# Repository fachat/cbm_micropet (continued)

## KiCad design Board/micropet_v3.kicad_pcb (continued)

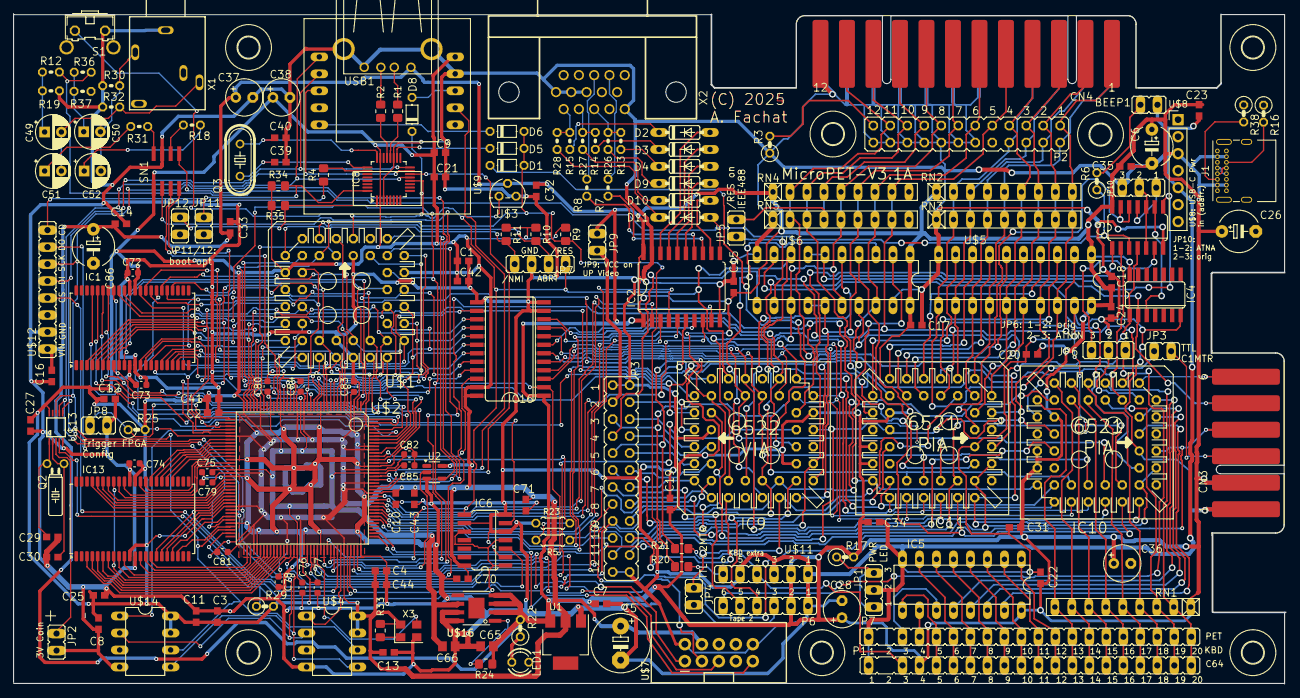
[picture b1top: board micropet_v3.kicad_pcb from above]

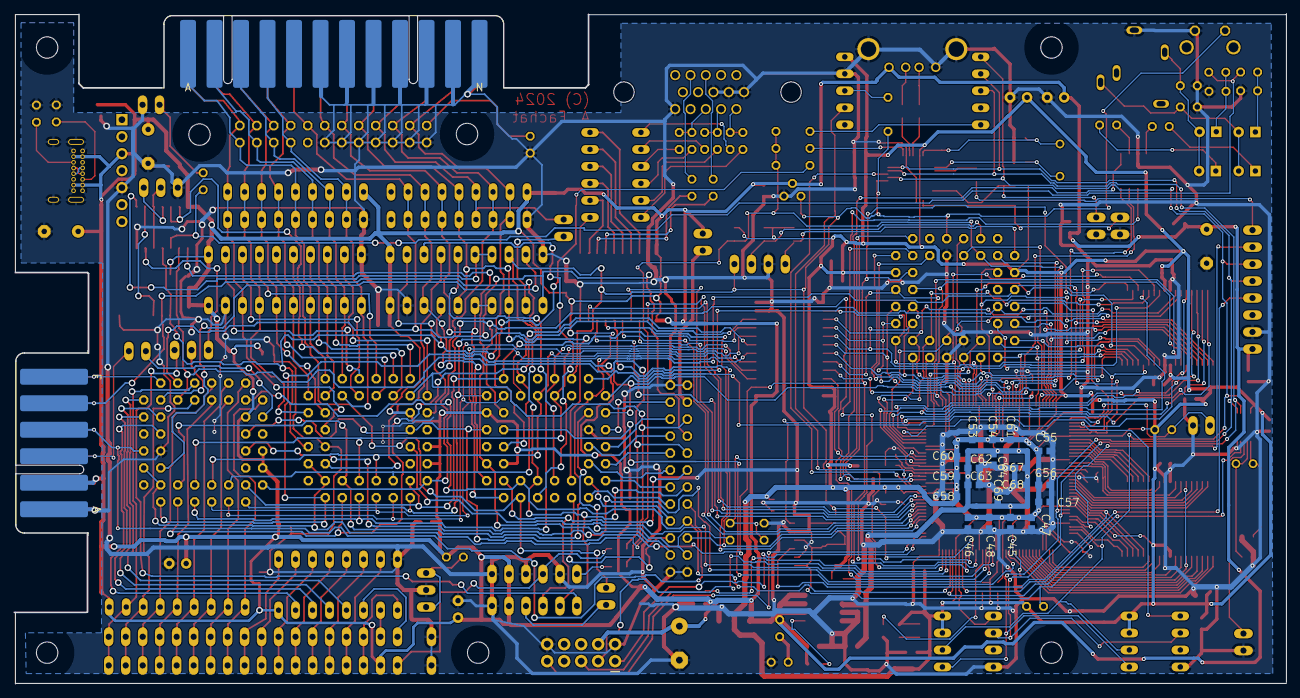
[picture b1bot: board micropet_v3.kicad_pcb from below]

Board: 2 copper layers, 190.2 x 100.3 mm, 204 parts (19 on the bottom side), 255 nets.

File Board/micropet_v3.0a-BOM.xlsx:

Designator | Footprint | Quantity | Orig | Value | MOUSER | MPN | Alternate
BEEP1 | JP2 | 1 |  | PIEZOBEEPER | 253-AE2038E4WA | AE-2038E-4WA |  | (To be put on cable to JP2)
C1, C12, C13, C14, C15, C16, C17, C18, C19, C2, C20, C21, C22, C23, C24, C25, C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 | C0603 | 49 |  | 0.1u | 710-885012206020 | 885012206020
C10, C11 | C0603 | 2 |  | 1u | 710-885012206020 | 885012206020
C26 | E2,5-6 | 1 |  | 47u | 710-860010372004 | 860010372004
C28, C36, C37, C38 | E2,5-6 | 4 |  | 22u | 710-860010372002 | 860010372002
C29, C30, C39, C40 | C0603 | 4 |  | 18p | 80-C0603C180K4HACTU | C0603C180K4HACTU |  |  | 77-VJ0603A180JXQCBC | VJ0603A180JXQCW1BC
C49, C50, C51, C52 | C050-025X075 | 4 |  | 1u | 710-860020672005 | 860020672005
C5 | E5-8,5 | 1 |  | 47u | 710-860010372004 | 860010372004
C6 | E5-6 | 1 |  | 47u | 710-860010372004 | 860010372004
C65, C66 | C0805 | 2 |  | 22u | 187-CL21A226MPQNNNE | CL21A226MPQNNNE
C7, C8 | C0603 | 2 |  | 100n | 710-885012206020 | 885012206020
C9 | C0603 | 1 |  | 1.0u Cer | 710-885012206020 | 885012206020
D1, D5, D6, D8 | D-5 | 4 |  | 1N4148 | 78-1N4148 | 1N4148TR |  |  | 512-1N4148 | 1N4148
D10, D11, D2, D3, D4, D9 | DO35-7 | 6 |  | 1N4148DO35-7 | 78-1N4148 | 1N4148TR |  |  | 512-1N4148 | 1N4148
H1, H2, H3, H4, H5, H6, H7 | 3.2 |  | 7 | MOUNT-HOLE3.2
IC1, IC13 | SOP32 | 2 |  | RAMSOCK32TO512KSOP | 870-61C5128AS-25QLI | IS61C5128AS-25QLI
IC10, IC11 | PLCC44 | 2 |  | PIAPLCC | 955-W65C21N6TPLG-14 | W65C21N6TPLG-14
IC16 | SO24L | 1 |  | 74LVC8T245SO24 | 595-SN74LVC4245ADW | SN74LVC4245ADW |  |  | 595-74LVC8T245DWRG4 | SN74LVC8T245DWRG4
IC2 | SO20W | 1 |  | 74245DW | 595-SN74HCT245DWR | SN74HCT245DWR
IC3 | SO14 | 1 |  | 7400D | 595-SN74HCT00DR | SN74HCT00DR
IC4 | SO14 | 1 |  | 7486D | 771-74HCT86D-T | 74HCT86D,653
IC5 | DIL16 | 1 |  | 74145N | 595-SN74LS145N | SN74LS145N | 595-SN74LS145NE4 | SN74LS145NE4
IC6 | SO14 | 1 |  | 74125D | 595-SN74LVC125AD | SN74LVC125AD
IC7 | SO16 | 1 |  | 74138D | 771-74LVC138AD-T | 74LVC138AD,118
IC8 | TQFP32-5MM | 1 |  | MAX3421E | 700-MAX3421EEHJT | MAX3421EEHJ+T
IC9 | PLCC44 | 1 |  | VIAPLCC | 955-W65C22N6TPLG-14 | W65C22N6TPLG-14
 | PLCC44 Socket | 4 |  |  | 517-8444-11B1-RK-TP | 8444-11B1-RK-TP
 | DIL16 Socket | 1 |  |  | 571-1-2199298-4 | 1-2199298-4
 | DIL20 Socket | 2 |  |  | 571-1-2199298-6 | 1-2199298-6
 | DIL08 Socket | 2 |  |  | 571-1-2199298-2 | 1-2199298-2
J1 | DCJ0202 | 1 |  | DCJ0202 | 806-KLDX-0202-A | KLDX-0202-A
JP1, JP10, JP6 | JP2 |  | 3 | JP2E
JP2, JP3, JP4, JP5, JP8, JP9 | JP1 |  | 6 | JP1E
JP7 | JP4 |  | 1 | JP4E
P6 | JP6 |  | 1 | CBMTAPE
P1 | C64KEYB |  | 1 | C64KEYB
P7 | C64KEYB |  | 1 | PETKEYBD
U$11 | JP6 |  | 1 | PETSKEY_EXTRA
U$8 | PinHeader_1x07_P2.54mm_Vertical |  | 1 | JP7
 |  | 3 |  | pin strip straight 20 pin | 649-1012937892001BLF | 10129378-920001BLF
JS1 | RENJS6 | 1 |  | RENOSCXLH | 972-XLH536070000000I | XLH536070.000000I
U$7 | FLAT10BOX | 1 |  | XILINXPROG | 710-61201021621 | 61201021621
LED1 | LED3MM | 1 |  | LED3MM | 696-SSL-LX305F4GD | SSL-LX305F4GD
P2 | FLAT24 | 1 |  | IEEE488FLATCABLE | 710-61202421621 | 61202421621
P3 | FLAT24 | 1 |  | PETUSERPORT | 710-61202421621 | 61202421621
Q1 | MICRO3 | 1 |  | IRLML5203 | 942-IRLML5203TRPBF | IRLML5203TRPBF
Q2 | TC26H | 1 |  | 32kHz | 710-830002995B | 830002995B
Q3 | HC49_S | 1 |  | 12MHz | 549-CYS6Q31C-12MHZ | CYS6Q31C-12.000MHZ
R20, R21, R6 | 0207_2V | 3 |  | 10 | 603-MF0207FTE26-10R | MF0207FTE26-10R
R1, R2, R4 | 0204_7 | 3 |  | 33 | 660-MF1/4LCT52R330J | MF1/4LCT52R330J
R7, R8 | 0204V | 2 |  | 68 | 660-MF1/4LCT52R680G | MF1/4LCT52R680G
R18, R31 | 0204V | 2 |  | 100 | 603-MFR-12FTF52-100R | MFR-12FTF52-100R
R29 | 0207_2V | 1 |  | 330 | 603-MFR-12FTF52-330R | MFR-12FTF52-330R
R17, R22 | 0207_2V | 2 |  | 390 | 756-MFR3-390RFC | MFR3-390RFC |  |  | 603-MFR-25FBF52-390R | MFR-25FBF52-390R
R13, R14, R15 | 0204V | 3 |  | 470 | 708-RNF14FTD470R | RNF14FTD470R
R30, R32 | 0204V | 2 |  | 680 | 603-MFR-12FTF52-680R | MFR-12FTF52-680R
R26, R27, R28 | 0204V | 3 |  | 1k | 603-MFR-12FTF52-1K | MFR-12FTF52-1K
R5 | 0204_5 | 1 |  | 2k2 | 603-MFR-12FTF52-2K2 | MFR-12FTF52-2K2
R3 | 0207_2V | 1 |  | 2k4 | 71-CCF072K40JKE36 | CCF072K40JKE36
R23 | 0204_5 | 1 |  | 3k3 | 603-MFR-12FTF52-3K3 | MFR-12FTF52-3K3
R25 | 0207_2V | 1 |  | 4k7 | 603-MFR-12FTF52-3K3 | MFR-12FTF52-4K7
R10, R11, R24, R9 | 0207_2V | 4 |  | 10k | 756-MFR3-10KFC | MFR3-10KFC
R16 | 0207_2V | 1 |  | 100k | 756-MFR3-100KFC | MFR3-100KFC
RN1 | RN-9 | 1 |  | 10k | 652-4609X-1LF-10K | 4609X-101-103LF
RN2, RN4 | RN-9 | 2 |  | 2k4 | 652-4609X-1LF-2.2K | 4609X-101-222LF
RN3, RN5 | RN-9 | 2 |  | 5k1 | 652-4609X-101-512LF | 4609X-101-512LF
S1 | B3F-31XX | 1 |  | 31-XX | 653-B3F-3122 | B3F-3122
SN1 | SOIC8 | 1 |  | MCP48X2 | 579-MCP4802-E/SN | MCP4802-E/SN
U$1 | PLCC44 | 1 |  | W65C816SPLCC | 955-W65C816S6PLG-14 | W65C816S6PLG-14
U$12 | GRAVITECH-SDCARD | 1 |  | SD-CARD-GRAVI | 992-MICROSD-ADP | MICROSD-ADP
 |  | 1 |  | Socket | 200-BCS108LSTE | BCS-108-L-S-TE
U$13 | MSOP10 | 1 |  | MCP79510 | 579-MCP79510-I/MS | MCP79510-I/MS
U$14, U$4 | DIL08 | 2 |  | SPIFLASH | 804-25VF080B5CPAE | SST25VF080B-50-4C-PAE |  |  | Other 4M/8M SPI Flash chips may work, mileage may vary (this Spartan6 req. > 2.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
U$16 | PSOP-8-FIXED | 1 |  | AP2132BB | 621-AP2132BMP1.2TRG1 | AP2132BMP-1.2TRG1
U$2 | TQFP144 | 1 |  | XC6SLX9-TQG144 | 217-XC6SLX9-2TQG144C | XC6SLX9-2TQG144C
U$3 | TO92 | 1 |  | DS1813 | 700-DS1818-10T&R | DS1818-10+T&R
U$5, U$6 | DIL20 | 2 |  | 74LS641 | 595-SN74LS641-1N | SN74LS641-1N
U$9 | ETHOLIENC | 1 |  | ETHOLIENC | 909-ENC28J60-H | ENC28J60-H
 |  | 2 |  |  | 200-BCS105LSTE | BCS-105-L-S-TE
U1 | SOT-223-3_TabPin2 | 1 |  | AMS1117-3.3 | 637-LDI1117-3.3H | LDI1117-3.3H
U2 | SOT-23-5 | 1 |  | 74LVC1G04 | 595-SN74LVC1G04DBVR | SN74LVC1G04DBVR
USB1 | USB-A-H | 1 |  | USB-A-H | 710-614004190021 | 614004190021
X1 | 1503_09 | 1 |  | 1503_09 | 490-SJ1-3513N | SJ1-3513N |  |  | Jack connectors according to JISC 6560, 3.5 mm
X2 | HDR15RA | 1 |  | D-SUB15-HDR15RA | 523-7HDE15SD1CH4FVGA | L77HDE15SD1CH4FVGA
CN3 | MA156_6-2_KEYED |  | 1 | PORT_CASSETTE_EDGE
CN4 | MA156_12-2_IEEE |  | 1 | PORT_IEEE_EDGE

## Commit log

2024-06-18 update to 3.0b, corrected gerbers
2024-06-19 update system arch diagram
2024-06-19 add version history
2024-06-20 add link to family repo
2024-06-26 handle (no) sub repos
2024-09-12 add mouser bom, fixes #3
2024-12-31 working on r3.1a
2025-01-02 draft final layout mupet 3.1a
2025-01-23 adapt audio output caps
2025-01-25 usb c connector
2025-01-25 final touches, 22u audio output caps
2025-01-25 production files
2025-01-25 update bom
2025-05-12 add 3D printable case
